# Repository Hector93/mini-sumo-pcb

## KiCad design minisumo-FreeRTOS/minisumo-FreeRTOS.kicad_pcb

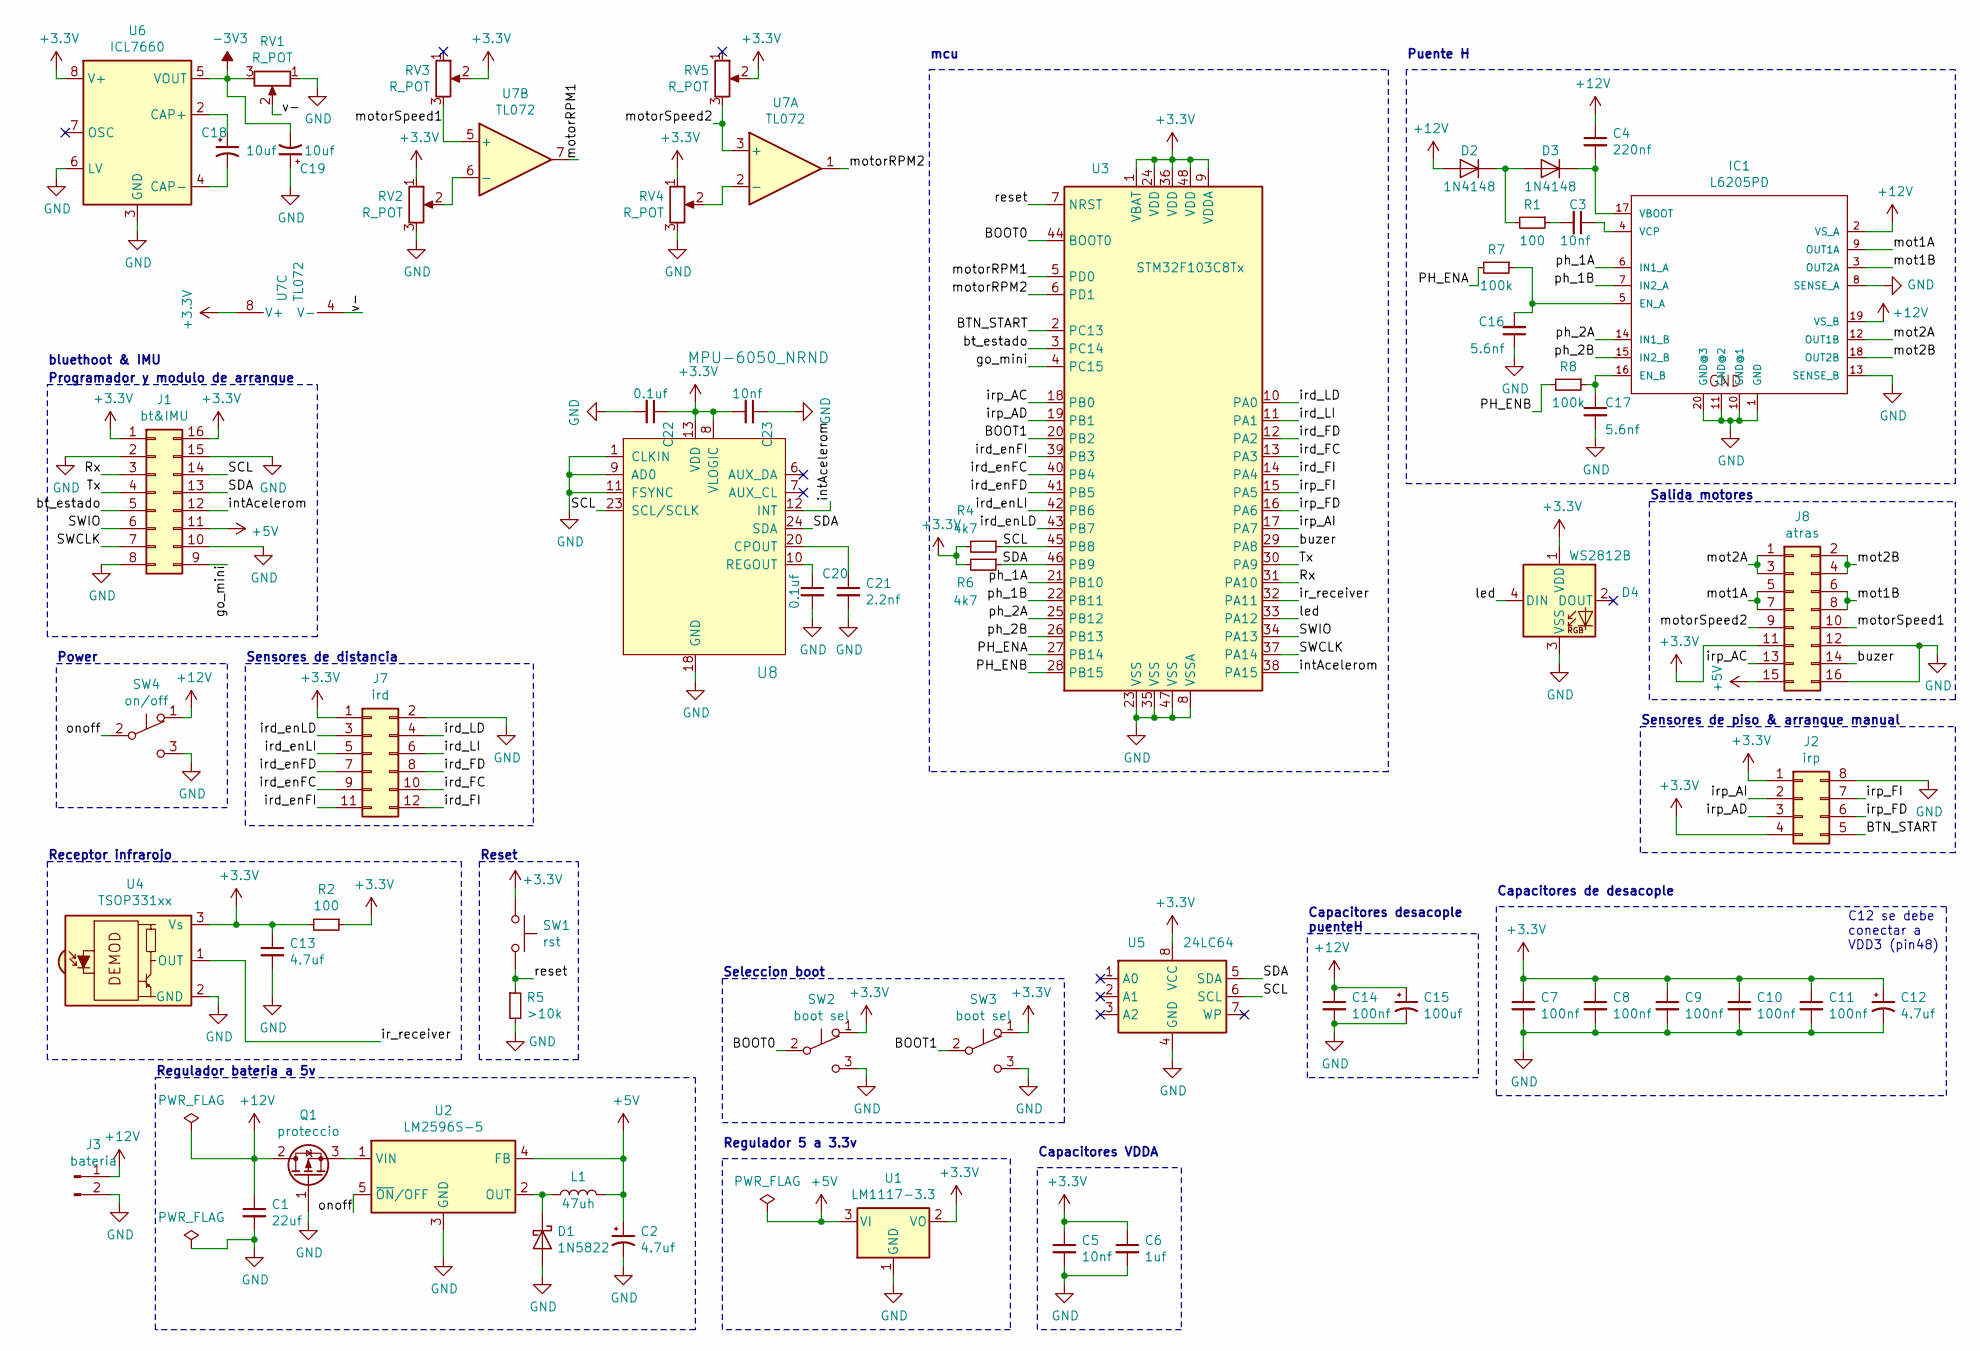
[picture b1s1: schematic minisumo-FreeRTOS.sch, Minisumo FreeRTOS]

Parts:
C1: 22uf; C_0603_1608Metric
C2: 4.7uf; CP_Elec_4x5.8
C3, C5, C23: 10nf; C_0603_1608Metric
C4: 220nf; C_0603_1608Metric
C6: 1uf; C_0603_1608Metric
C7, C8, C9, C10, C11, C14: 100nf; C_0603_1608Metric
C12, C13: 4.7uf; R_0603_1608Metric
C15: 100uf; CP_Elec_4x3
C16, C17: 5.6nf; C_0603_1608Metric
C18, C19: 10uf; CP_Elec_4x5.8
C20, C22: 0.1uf; CP_EIA-3216-18_Kemet-A
C21: 2.2nf; C_0603_1608Metric
D1: 1N5822; D_DO-201AD_P15.24mm_Horizontal
D2, D3: 1N4148; D_SOD-323F
D4: WS2812B; LED_WS2812B_PLCC4_5.0x5.0mm_P3.2mm
IC1: L6205PD; HSOP-20-1EP_11.0x15.9mm_P1.27mm_SlugUp
J1: bt&IMU; PinSocket_2x08_P1.27mm_Vertical_SMD
J2: irp; PinSocket_2x04_P1.27mm_Vertical_SMD
J3: bateria; PinHeader_1x02_P2.54mm_Vertical
J7: ird; PinSocket_2x06_P1.27mm_Vertical_SMD
J8: atras; PinSocket_2x08_P1.27mm_Vertical_SMD
L1: 47uh; L_7.3x7.3_H4.5
Q1: proteccio; TO-252-2
R1, R2: 100; R_0603_1608Metric
R4, R6: 4k7; R_0603_1608Metric
R5: >10k; R_0603_1608Metric
R7, R8: 100k; R_0603_1608Metric
RV1, RV2, RV3, RV4, RV5: R_POT; Potentiometer_Trimmer-EVM3E
SW1: rst; SW_SPST_TL3342
SW2, SW3: boot sel; SolderJumper-3_P1.3mm_Open_RoundedPad1.0x1.5mm
SW4: on/off; SW_SPDT_PCM12
U1: LM1117-3.3; SOT-223-3_TabPin2
U2: LM2596S-5; TO-263-5_TabPin3
U3: STM32F103C8Tx; LQFP-48_7x7mm_P0.5mm
U4: TSOP331xx; Vishay_MINIMOLD-3Pin
U5: 24LC64; SOIC-8_3.9x4.9mm_P1.27mm
U6: ICL7660; SOIC-8_3.9x4.9mm_P1.27mm
U7: TL072; SOIC-8_3.9x4.9mm_P1.27mm
U8: MPU-6050_NRND; QFN-24-1EP_4x4mm; MPN MPU-6050; Digi-Key_PN 1428-1007-1-ND

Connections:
+3V3: C5.1, C6.1, C7.1, C8.1, C9.1, C10.1, C11.1, C12.1, C13.1, C22.1, C23.2, D4.1 (VDD), J1.1, J1.16, J2.1, J2.4, J7.1, J8.11, R2.1, R2.2, R4.2, R6.2, RV2.1, RV3.2, RV4.1, RV5.2, SW1.1, SW2.1 (A), SW3.1 (A), U1.2 (VO), U3.1 (VBAT), U3.9 (VDDA), U3.24 (VDD), U3.36 (VDD), U3.48 (VDD), U4.3 (Vs), U5.8 (VCC), U6.8 (V+), U7.8 (V+), U8.8 (VLOGIC), U8.13 (VDD); also elsewhere on the board
+5V: C2.1, J1.11, J8.15, L1.2, U1.3 (VI), U2.4 (FB)
+12V: C1.1, C4.1, C14.1, C15.1, D2.2 (A), IC1.2 (VS_A), IC1.19 (VS_B), J3.1, Q1.2 (D), SW4.1 (A)
-3V3: C19.2, RV1.3, U6.5 (VOUT)
/BOOT0: SW2.2 (B), U3.44 (BOOT0)
/BOOT1: SW3.2 (B), U3.20 (PB2)
/BTN_START: J2.5, U3.2 (PC13)
/PH_ENA: R7.2, U3.27 (PB14)
/PH_ENB: R8.2, U3.28 (PB15)
/Rx: J1.3, U3.31 (PA10)
/SCL: J1.14, R4.1, U3.45 (PB8), U5.6 (SCL), U8.23 (SCL/SCLK)
/SDA: J1.13, R6.1, U3.46 (PB9), U5.5 (SDA), U8.24 (SDA)
/SWCLK: J1.7, U3.37 (PA14)
/SWIO: J1.6, U3.34 (PA13)
/Tx: J1.4, U3.30 (PA9)
/bt_estado: J1.5, U3.3 (PC14)
/buzer: J8.14, U3.29 (PA8)
/go_mini: J1.9, U3.4 (PC15)
/intAcelerom: J1.12, U3.38 (PA15), U8.12 (INT)
/ir_receiver: U3.32 (PA11), U4.1 (OUT); also elsewhere on the board
/ird_FC: J7.10, U3.13 (PA3)
/ird_FD: J7.8, U3.12 (PA2)
/ird_FI: J7.12, U3.14 (PA4)
/ird_LD: J7.4, U3.10 (PA0)
/ird_LI: J7.6, U3.11 (PA1)
/ird_enFC: J7.9, U3.40 (PB4)
/ird_enFD: J7.7, U3.41 (PB5)
/ird_enFI: J7.11, U3.39 (PB3)
/ird_enLD: J7.3, U3.43 (PB7)
/ird_enLI: J7.5, U3.42 (PB6)
/irp_AC: J8.13, U3.18 (PB0)
/irp_AD: J2.3, U3.19 (PB1)
/irp_AI: J2.2, U3.17 (PA7)
/irp_FD: J2.6, U3.16 (PA6)
/irp_FI: J2.7, U3.15 (PA5)
/led: D4.4 (DIN), U3.33 (PA12)
/mot1A: IC1.9 (OUT1A), J8.5, J8.7
/mot1B: IC1.3 (OUT2A), J8.6, J8.8
/mot2A: IC1.12 (OUT1B), J8.1, J8.3
/mot2B: IC1.18 (OUT2B), J8.2, J8.4
/motorRPM1: U3.5 (PD0), U7.7
/motorRPM2: U3.6 (PD1), U7.1
/motorSpeed1: J8.10, RV3.3, U7.5 (+)
/motorSpeed2: J8.9, RV5.3, U7.3 (+)
/onoff: SW4.2 (B), U2.5 (~ON~/OFF)
/ph_1A: IC1.6 (IN1_A), U3.21 (PB10)
/ph_1B: IC1.7 (IN2_A), U3.22 (PB11)
/ph_2A: IC1.14 (IN1_B), U3.25 (PB12)
/ph_2B: IC1.15 (IN2_B), U3.26 (PB13)
/reset: R5.1, SW1.2, U3.7 (NRST)
/v-: RV1.2, U7.4 (V-)
GND: C1.2, C2.2, C5.2, C6.2, C7.2, C8.2, C9.2, C10.2, C11.2, C12.2, C13.2, C14.2, C15.2, C16.1, C17.2, C19.1, C20.2, C21.2, C22.2, C23.1, D1.2 (A), D4.3 (VSS), IC1.1 (GND), IC1.8 (SENSE_A), IC1.10 (GND@1), IC1.11 (GND@2), IC1.13 (SENSE_B), IC1.20 (GND@3), J1.2, J1.8, J1.10, J1.15, J2.8, J3.2, J7.2, J8.12, J8.16, Q1.1 (G), R5.2, RV1.1, RV2.3, RV4.3, SW2.3 (C), SW3.3 (C), SW4.3 (C), U1.1 (GND), U2.3 (GND), U3.8 (VSSA), U3.23 (VSS), U3.35 (VSS), U3.47 (VSS), U4.2 (GND), U5.4 (GND), U6.3 (GND), U6.6 (LV), U8.1 (CLKIN), U8.9 (AD0), U8.11 (FSYNC), U8.18 (GND)
unnamed: C3.1, IC1.4 (VCP)
unnamed: C3.2, R1.1
unnamed: C4.2, D3.1 (K), IC1.17 (VBOOT)
unnamed: C16.2, IC1.5 (EN_A), R7.1
unnamed: C17.1, IC1.16 (EN_B), R8.1
unnamed: C18.1, U6.2 (CAP+)
unnamed: C18.2, U6.4 (CAP-)
unnamed: C20.1, U8.10 (REGOUT)
unnamed: C21.1, U8.20 (CPOUT)
unnamed: D1.1 (K), L1.1, U2.2 (OUT)
unnamed: D2.1 (K), D3.2 (A), R1.2
unnamed: Q1.3 (S), U2.1 (VIN)
unnamed: RV2.2, U7.6 (-)
unnamed: RV4.2, U7.2 (-)

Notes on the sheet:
Capacitores de desacople
Capacitores VDDA
C12 se debe conectar a VDD3 (pin48)
Regulador bateria a 5v
Regulador 5 a 3.3v
Receptor infrarojo
Puente H
mcu
bluethoot & IMU
Sensores de distancia
Salida motores
Seleccion boot
Reset
Power
Programador y modulo de arranque
Sensores de piso & arranque manual
Capacitores desacople puenteH

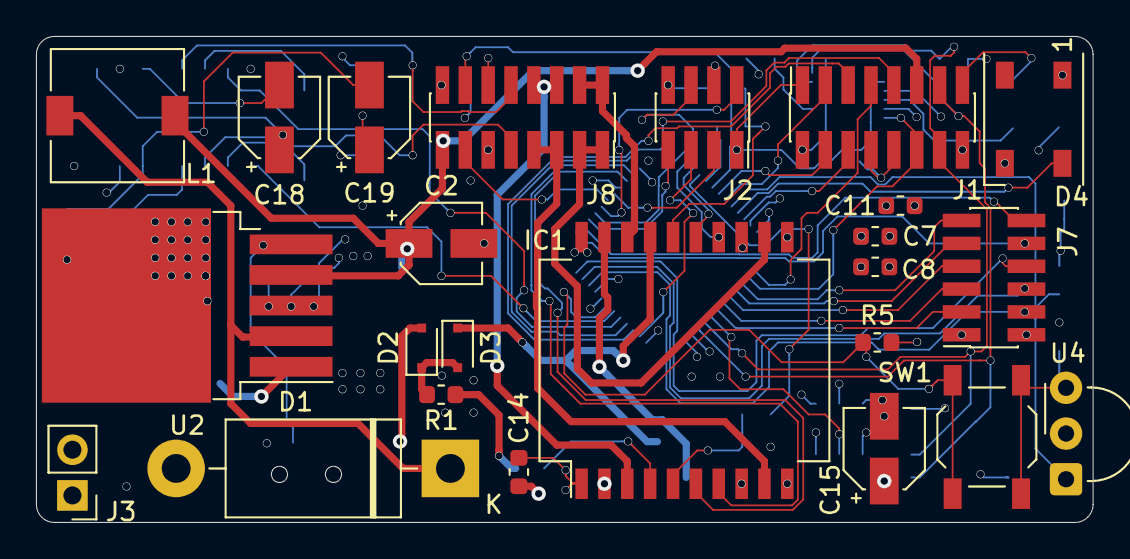
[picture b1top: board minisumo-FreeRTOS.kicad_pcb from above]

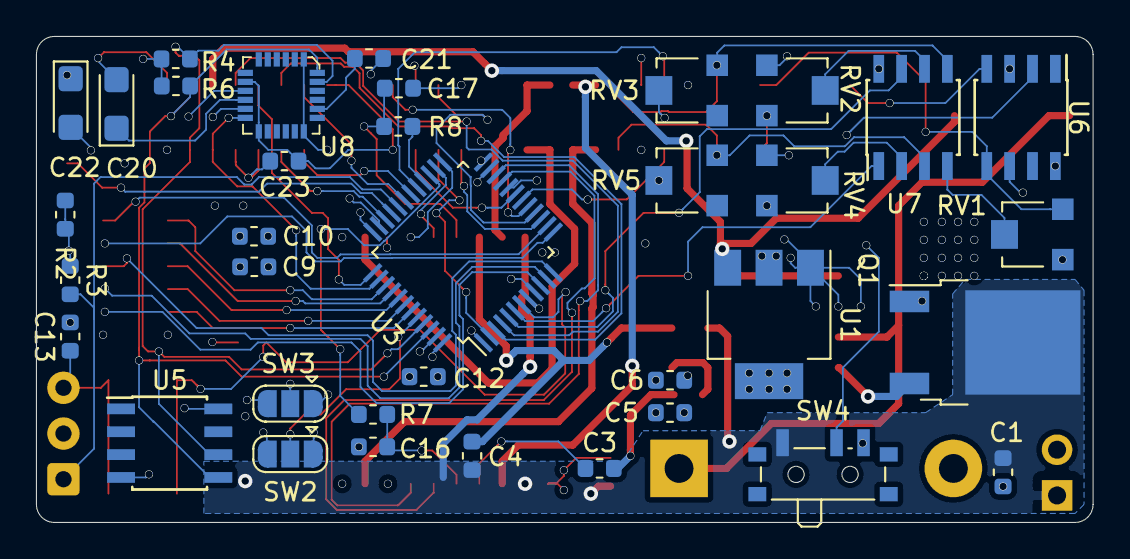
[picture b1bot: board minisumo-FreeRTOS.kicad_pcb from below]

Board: 4 copper layers, 58.7 x 27.0 mm, 60 parts (36 on the bottom side), 66 nets.

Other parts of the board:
R3: >20k; R_0603_1608Metric

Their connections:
+3V3: R3.1; also elsewhere on the board
/ir_receiver: R3.2; also elsewhere on the board

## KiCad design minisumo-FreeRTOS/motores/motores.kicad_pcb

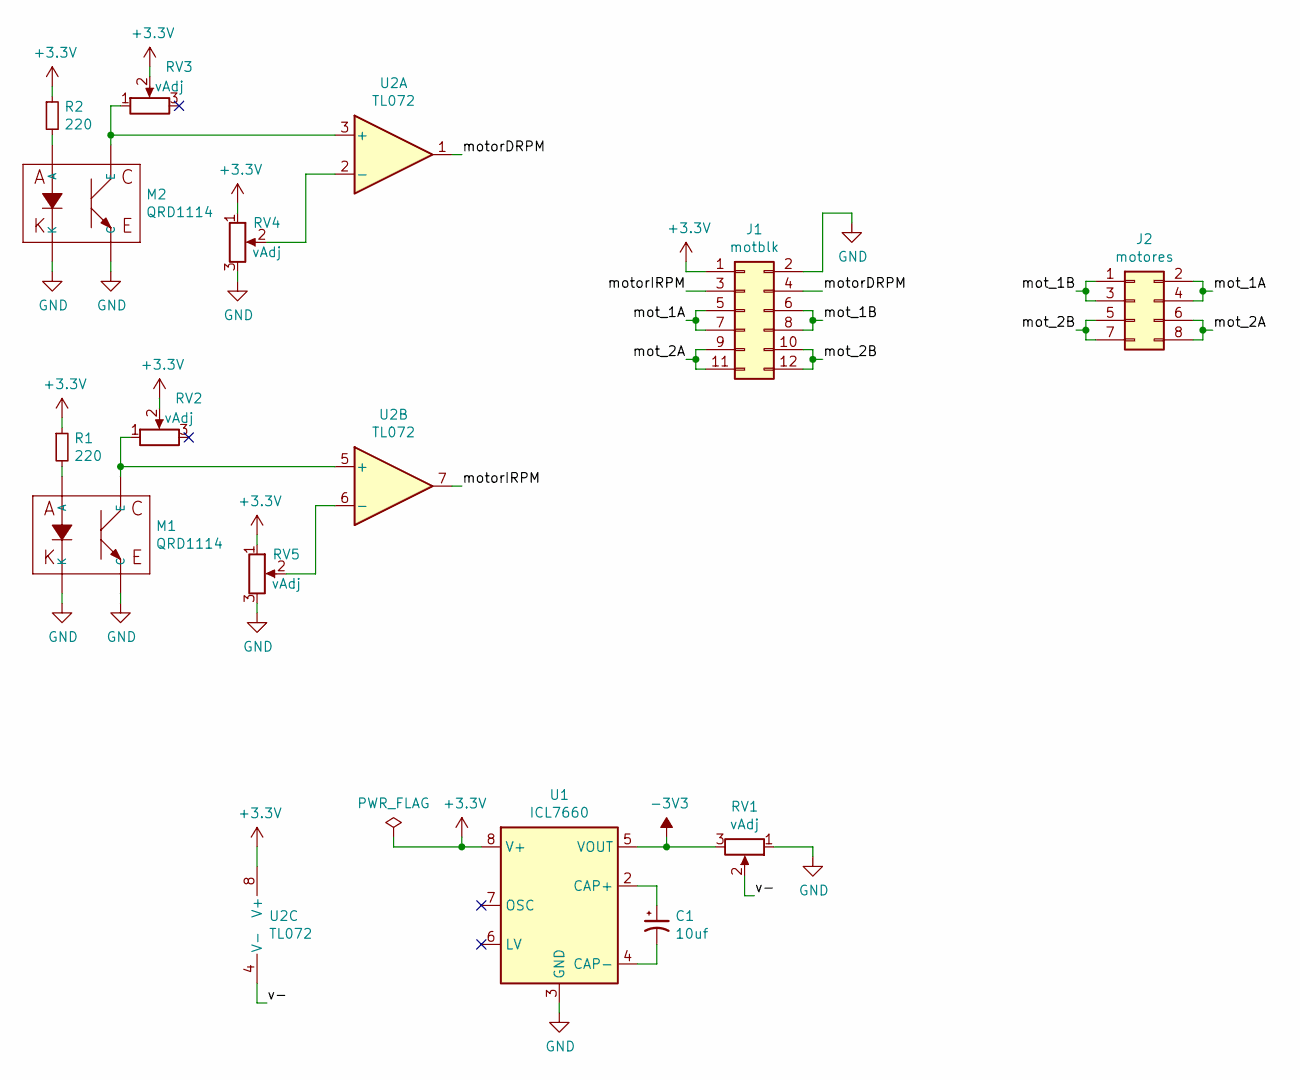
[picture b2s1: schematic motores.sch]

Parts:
C1: 10uf; CP_Elec_4x5.4
J1: motblk; PinSocket_2x06_P1.27mm_Vertical_SMD
J2: motores; PinSocket_2x04_P1.27mm_Vertical_SMD
M1, M2: QRD1114; PinSocket_2x02_P1.27mm_Vertical_SMD
R1, R2: 220; R_0603_1608Metric
RV1, RV2, RV3, RV4, RV5: vAdj; Potentiometer_Trimmer-EVM3E
U1: ICL7660; SOIC-8_3.9x4.9mm_P1.27mm
U2: TL072; SOIC-8_3.9x4.9mm_P1.27mm

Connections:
+3V3: J1.1, R1.1, R2.1, RV2.2, RV3.2, RV4.1, RV5.1, U1.8 (V+), U2.8 (V+)
-3V3: RV1.3, U1.5 (VOUT)
/mot_1A: J1.5, J1.7, J2.2, J2.4
/mot_1B: J1.6, J1.8, J2.1, J2.3
/mot_2A: J1.9, J1.11, J2.6, J2.8
/mot_2B: J1.10, J1.12, J2.5, J2.7
/motorDRPM: J1.4, U2.1
/motorIRPM: J1.3, U2.7
/v-: RV1.2, U2.4 (V-)
GND: J1.2, M1.2 (C), M1.4 (K), M2.2 (C), M2.4 (K), RV1.1, RV4.3, RV5.3, U1.3 (GND)
unnamed: C1.1, U1.2 (CAP+)
unnamed: C1.2, U1.4 (CAP-)
unnamed: M1.1 (E), RV2.1, U2.5 (+)
unnamed: M1.3 (A), R1.2
unnamed: M2.1 (E), RV3.1, U2.3 (+)
unnamed: M2.3 (A), R2.2
unnamed: RV4.2, U2.2 (-)
unnamed: RV5.2, U2.6 (-)

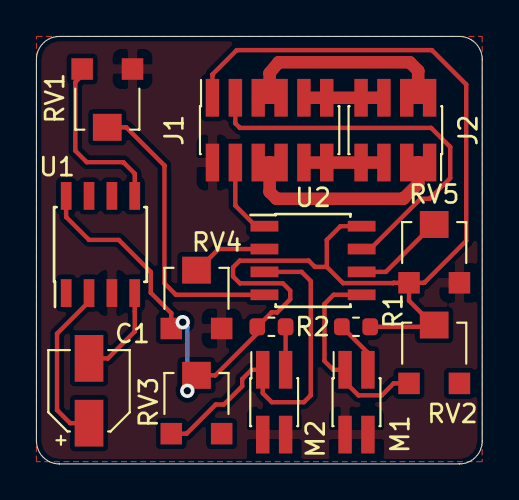
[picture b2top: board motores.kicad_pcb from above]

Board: 2 copper layers, 24.8 x 23.7 mm, 14 parts (0 on the bottom side), 18 nets.
